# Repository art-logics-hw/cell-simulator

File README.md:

# Cell Simulator

Battery cell simulator hardware design

## Issues

* [ ] `CAN1_TX` and `CAN1_RX` is swapped.
* [ ] R32 (120ohm) between `CAN1_TX` and `CAN1_RX` should be removed.
* [ ] Add 100ohm, 0.5W resistor between GND and V- of U19 DC-DC module for positive/negative balancing.

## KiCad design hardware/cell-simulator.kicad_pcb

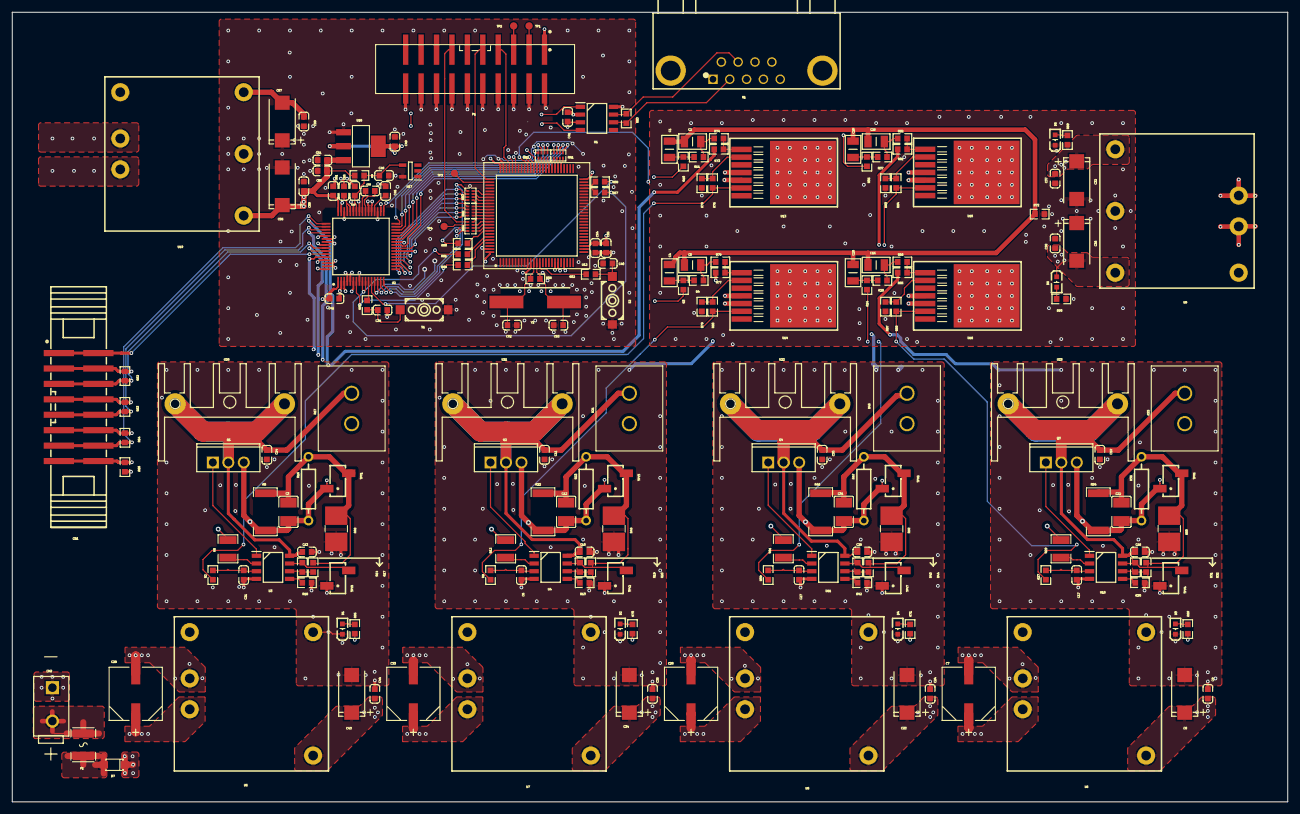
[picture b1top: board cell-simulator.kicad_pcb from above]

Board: 4 copper layers, 210.0 x 130.0 mm, 201 parts (0 on the bottom side), 156 nets.

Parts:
C1, C2, C4, C5, C15, C16, C25, C26: CAPC3216X190N
C3, C12, C22, C31: C1210
C6, C9, C10, C11, C13, C14, C17, C18, C19, C21, C24, C27, C28, C30, C35, C37, C38, C39, C40, C41, C42, C44, C45, C46, C47, C48, C49, C50, C51, C52, C53, C54, C55, C58, C59, C60, C61: LC-0603_C
C7, C20, C29, C33: CAP_J-V_8X10P5_RUB
C8, C23, C32, C34, C36, C43, C56, C57: CAPPM7343X310N
CN1: IDC-SMD_16P-P2.54_Z-S230321016M2BLT1
CN2: 39-28-8020
D1, D2, D3, D4, D5, D6: LED0603-R-RD
D7: SOD-123FL_L2.7-W1.8-LS3.8-RD
F1: F1812
P1: CONN-SMD_20P-P2.54_B-3000N20P-0110
Q1, Q2, Q3, Q4: TO255P460X1020X2008-3P
R2, R3, R4, R8, R10, R11, R13, R14, R17, R18, R19, R20, R24, R25, R27, R30, R31, R32, R36, R37, R39, R42, R43, R44, R51, R52, R53, R55, R56, R57, R58, R59, R60, R61, R62, R63, R64, R65, R66, R69, R70, R71, R72, R73, R74, R75, R76, R77, R78, R79, R80, R81, R82, R83, R84, R85, R86, R87, R88, R89, R90: LC-0603_R
R5, R22, R34, R46: R2512
R6, R12, R29, R41: R1210
R16, R23, R35, R47: MF0W4FF6801A50
R21, R33, R45, R67: RX27-5
R48, R49, R50, R68: PA2512FKE7W0R001E
RN1, RN2, RN3, RN4, RN5: RES-ARRAY-SMD_0402-8P-L2.0-W1.0-BL
S1, S2: KEY-SMD_L6.2-W3.6-LS8.0
TP1, TP2, TP3, TP4: PAD-1.2
TPV1, TPV2, TPV3, TPV4, TPV5, TPV6, TPV7, TPV8: HDR-SMD_2P-P2.54-V-M-S4.8
U1: SOIC127P600X175-8N
U2: QFP50P1200X1200X160-64N
U3, U4, U10, U11: LM2904BQDRQ1
U5, U6, U7, U8: URBXXXXYMD-10WR3
U9, U19: URAXXXXYMD-10WR3
U12: QFP50P1600X1600X160-100N
U13, U14, U15, U16: KTW7
U17: SOT95P280X145-5N
U18: SOT-223_L6.5-W3.5-P2.30-LS7.0-BR
U20, U21, U22, U23: HEATSINK-TH_L23.5-W16.0-P18.0_XSD2156-06
X1: DSUB-TH_DMR-9S
Y1: ABLS-12.000MHZ-B2

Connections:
2V5REF: C47.2, C48.1, R55.2, U2.42, U17.4
$$$1152: C3.1, R5.1, R16.1, R17.1, R48.2, TPV1.2
$$$1196: C12.1, R20.1, R22.1, R23.1, R49.2, TPV3.2
$$$1298: C22.1, R32.1, R34.1, R35.1, R50.2, TPV6.2
$$$1418: C31.1, R44.1, R46.1, R47.1, R68.2, TPV8.2
$$$1466: C6.1, R8.2, U4.3
$$$1467: R12.1, U4.2
$$$1468: C4.2, R3.2, R4.1
$$$1469: Q2.1, U4.1
$$$1470: C10.1, C11.1, Q2.2, R21.1, U4.8, U21.1, U21.2
$$$1471: R19.1, TPV2.2, U4.7
$$$1472: R13.2, U4.5
$$$1473: R19.2, R20.2, U4.6
$$$1474: C17.1, R27.2, U10.3
$$$1475: R29.1, U10.2
$$$1476: C15.2, R24.2, R25.1
$$$1477: Q3.1, U10.1
$$$1478: C18.1, C19.1, Q3.2, R33.1, U10.8, U23.1, U23.2
$$$1479: R31.1, TPV4.2, U10.7
$$$1480: R30.2, U10.5
$$$1481: R31.2, R32.2, U10.6
$$$1482: C27.1, R39.2, U11.3
$$$1483: R41.1, U11.2
$$$1484: C25.2, R36.2, R37.1
$$$1485: Q4.1, U11.1
$$$1486: C28.1, C30.1, Q4.2, R45.1, U11.8, U22.1, U22.2
$$$1487: R43.1, TPV7.2, U11.7
$$$1488: R42.2, U11.5
$$$1489: R43.2, R44.2, U11.6
$$$3411: R6.1, U3.2
$$$3420: C21.1, R2.2, U3.3
$$$4490: C1.2, R10.2, R11.1
$$$7976: P1.3, TP1.1
$$$7978: P1.5, TP2.1
$$$8071: TP3.1, U12.77
$$$8097: RN4.7, TP4.1
$$$10062: Q1.1, U3.1
$$$10192: C13.1, C14.1, Q1.2, R67.1, U3.8, U20.1, U20.2
$$$10374: R14.1, TPV5.2, U3.7
$$$10421: R18.2, U3.5
$$$10474: R14.2, R17.2, U3.6
$$$12937: D7.2, F1.2
$$$15374: R73.2, R74.2, U13.1
$$$15480: R75.2, R76.1, U13.2
$$$15551: R77.2, R78.2, U14.1
$$$15552: R79.2, R80.1, U14.2
$$$15559: R81.2, R82.2, U15.1
$$$15560: R83.2, R84.1, U15.2
$$$15562: R85.2, R86.2, U16.1
$$$15563: R87.2, R88.1, U16.2
$$$16325: CN2.2, F1.1
$$$16602: D5.1, R89.1
$$$16631: D6.1, R90.1
$$$18206: C39.1, R51.2, S1.1
$$$18291: C40.1, R52.2, S2.1
$$$18913: R53.1, U1.6, X1.2
$$$18918: R53.2, U1.7, X1.7
$$$20459: C46.1, U2.36
$$$24853: D1.1, R66.2
$$$24877: D3.1, R69.2
$$$24913: D4.1, R71.2
$$$24942: D2.1, R70.2
$$$28916: C52.2, R56.2, U12.12, Y1.2
$$$28919: C53.2, R56.1, U12.13, Y1.1
$$$29529: R57.2, U12.47
$$$29530: R58.2, U12.48
$$$29769: RN1.4, U12.58
$$$29771: RN1.3, U12.57
$$$29772: RN1.2, U12.56
$$$29773: RN1.1, U12.55
$$$29939: RN2.4, U12.62
$$$30112: RN2.1, U12.59
$$$30117: RN2.2, U12.60
$$$30238: RN2.3, U12.61
$$$30640: RN5.1, U12.85
$$$30641: RN5.2, U12.86
$$$30643: RN5.3, U12.87
$$$30645: RN5.4, U12.88
$$$30652: RN3.4, U12.84
$$$30655: RN3.3, U12.83
$$$30661: RN3.2, U12.82
$$$30664: RN3.1, U12.81
$$$30684: RN4.1, U12.89
$$$30687: RN4.2, U12.90
$$$30690: RN4.3, U12.91
$$$30693: RN4.4, U12.92
$$$31167: R60.1, U12.93
$$$31288: R61.1, U12.95
$$$31389: R59.1, U12.96
$$$31870: C57.1, C59.2, U19.5
$$$32347: C45.1, U2.40
$$$32491: C45.2, U2.39
$$$32715: C60.1, U2.44, U2.45
+3V3: C49.1, C54.2, C55.2, P1.1, U2.23, U12.11, U12.19, U12.22, U12.28, U12.50, U12.75, U12.100, U18.2, U18.4
+5V: C41.2, C42.1, C50.1, C51.1, C56.2, C58.1, C61.1, R55.1, U1.3, U2.1, U2.37, U2.38, U2.48, U18.3, U19.3
+9V_1: C43.2, C44.2, R66.1, R67.2, U5.3
+9V_2: C34.2, C35.2, R21.2, R70.1, U7.3
+9V_3: C23.2, C24.2, R45.2, R71.1, U8.3
+9V_4: C8.2, C9.2, R33.2, R69.1, U6.3
+24V: C7.1, C20.1, C29.1, C33.1, D7.1, U5.2, U6.2, U7.2, U8.2, U9.2, U19.2
-24V: C7.2, C20.2, C29.2, C33.2, CN2.1, U5.1, U6.1, U7.1, U8.1, U9.1, U19.1
AD1RST: R51.1, U2.11
BUSY: U2.14, U12.71
C1: C3.2, CN1.13, CN1.14, Q1.3, R5.2, R6.2, R16.2, R64.2, TPV1.1, U2.49
C1A: C2.2, R11.2, R74.1
C1D: R10.1, U12.63
C1I: R2.1, R76.2, U13.6
C2: C12.2, CN1.9, CN1.10, Q2.3, R22.2, R23.2, R63.2, TPV3.1, U2.51
C2A: C5.2, R4.2, R78.1
C2D: R3.1, U12.64
C2I: R8.1, R80.2, U14.6
C3: C31.2, CN1.5, CN1.6, Q4.3, R41.2, R46.2, R47.2, R62.2, TPV8.1, U2.57
C3A: C26.2, R37.2, R82.1
C3D: R36.1, U12.65
C3I: R39.1, R84.2, U15.6
C4: C22.2, CN1.1, CN1.2, Q3.3, R29.2, R34.2, R35.2, TPV6.1, U2.59
C4A: C16.2, R25.2, R86.1
C4D: R24.1, U12.66
C4I: R27.1, R88.2, U16.6
CAN1_RX: RN4.6, U1.4
CAN1_TX: RN4.5, U1.1
CHIPSELECT#: U2.13, U12.70
CONVSTART: R57.1, R61.2, U2.9, U2.10
D0: RN3.8, U2.16
D1: RN3.7, U2.17
D2: RN3.6, U2.18
D3: RN3.5, U2.19
D4: RN5.8, U2.20
D5: RN5.7, U2.21
D6: RN5.6, U2.22
D7: RN5.5, U2.24
D8: RN1.8, U2.25
D9: RN1.7, U2.27
D10: RN1.6, U2.28
D11: RN1.5, U2.29
D12: RN2.8, U2.30
D13: RN2.7, U2.31
D14: RN2.6, U2.32
D15: RN2.5, U2.33
EPAD: U13.8, U14.8, U15.8, U16.8
FIRSTDATA: R60.2, U2.15
GND: C39.2, C40.2, C41.1, C42.2, C46.2, C47.1, C48.2, C49.2, C50.2, C51.2, C52.1, C53.1, C54.1, C55.1, C56.1, C57.2, C58.2, C59.1, C60.2, C61.2, P1.2, P1.4, P1.6, P1.8, P1.10, P1.12, P1.14, P1.16, P1.18, P1.20, S1.2, S2.2, U1.2, U1.8, U2.2, U2.3, U2.4, U2.5, U2.6, U2.8, U2.26, U2.34, U2.35, U2.41, U2.43, U2.46, U2.47, U2.53, U2.54, U2.55, U2.56, U2.61, U2.62, U2.63, U2.64, U12.10, U12.20, U12.27, U12.74, U12.99, U17.5, U18.1, U19.4
GND1: C13.2, C14.2, C21.2, C43.1, C44.1, CN1.15, CN1.16, D1.2, R18.1, R48.1, R65.1, R73.1, TPV5.1, U2.50, U3.4, U5.5
GND2: C6.2, C10.2, C11.2, C34.1, C35.1, CN1.11, CN1.12, D2.2, R13.1, R49.1, R64.1, R77.1, TPV2.1, U2.52, U4.4, U7.5
GND3: C23.1, C24.1, C27.2, C28.2, C30.2, CN1.7, CN1.8, D4.2, R42.1, R63.1, R68.1, R81.1, TPV7.1, U2.58, U8.5, U11.4
GND4: C8.1, C9.1, C17.2, C18.2, C19.2, CN1.3, CN1.4, D3.2, R30.1, R50.1, R62.1, R85.1, TPV4.1, U2.60, U6.5, U10.4
ISO24V+: C32.2, C37.1, R89.2, U9.3, U13.5, U14.5, U15.5, U16.5
ISO24V-: C36.1, C38.2, D6.2, U9.5, U13.4, U14.4, U15.4, U16.4
ISOGND: C32.1, C36.2, C37.2, C38.1, D5.2, R65.2, R72.1, R75.1, R79.1, R83.1, R87.1, R90.2, U9.4
MCURST: R52.1, U12.14
PA13: P1.7, U12.72
PA14: P1.9, U12.76
PB3: P1.13, RN4.8
READDATA#: R58.1, U2.12
SGND: C1.1, C2.1, C4.1, C5.1, C15.1, C16.1, C25.1, C26.1, R72.2
STANDBY#: R59.2, U2.7

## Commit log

2022-05-30 add git ignore file.
2022-05-30 add README.
2022-05-30 add kicad design files imported from EasyEDA.
2022-05-30 update gitignore.
2022-06-06 doc.
2022-06-06 add DC-DC module balancing issue and solution.
2022-06-15 add schematic and pcb exported from PADs.
2022-06-15 refactoring.
2022-07-04 Refactoring and CAN Fix: * refactoring overlapped net lebels around MCU and ADC * remove MCU-side 120ohm resister on CAN Tranceiver * fix: swap CAN RX/TX * fix: PA11/12 <----> PB5/6
2022-07-04 update OP amp circuit, update PCB.
2022-07-05 add FIU relay schematics.
2022-07-05 add lib files to repo.
2022-07-06 update PCB.
2022-07-06 add 100ohm load resistor on -5V of DC-DC module.
2022-07-07 add mounting holes.
2022-07-07 update Sch and PCB: fix MCURST, remove A1RST, fix ADC inputs, improve mounting holes.
2022-07-07 fix JTAG.
